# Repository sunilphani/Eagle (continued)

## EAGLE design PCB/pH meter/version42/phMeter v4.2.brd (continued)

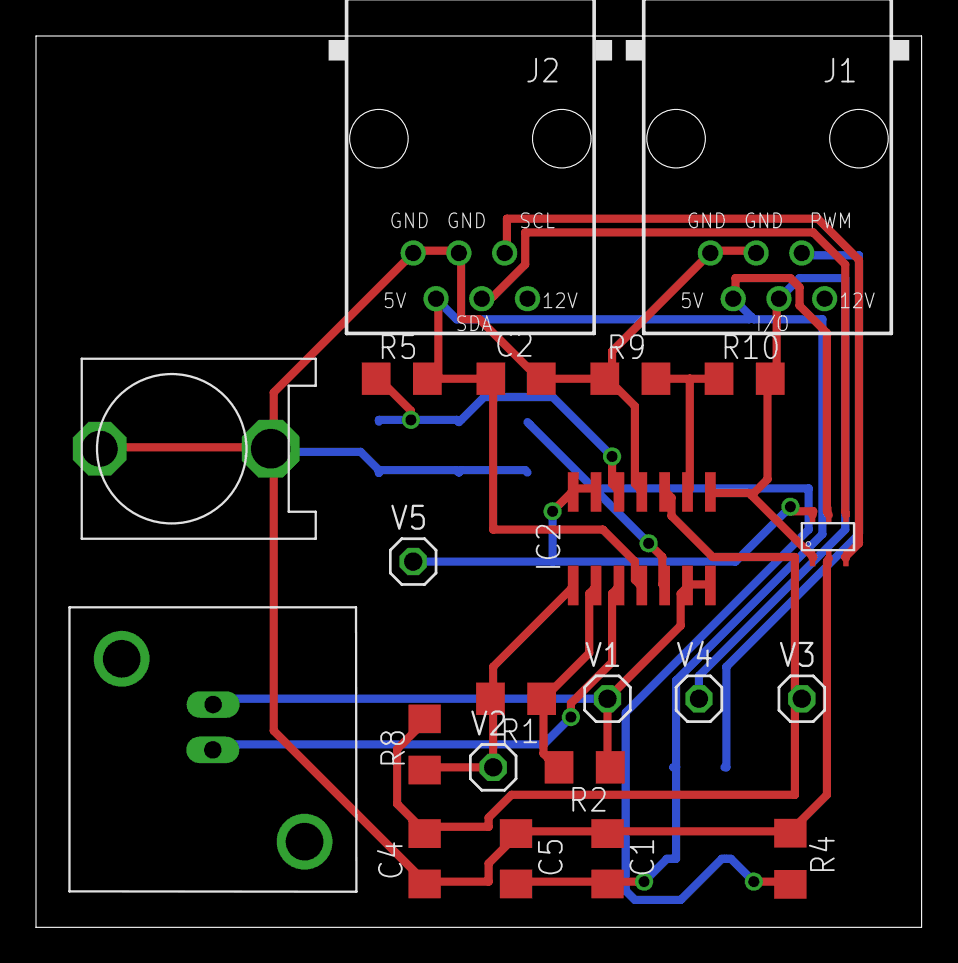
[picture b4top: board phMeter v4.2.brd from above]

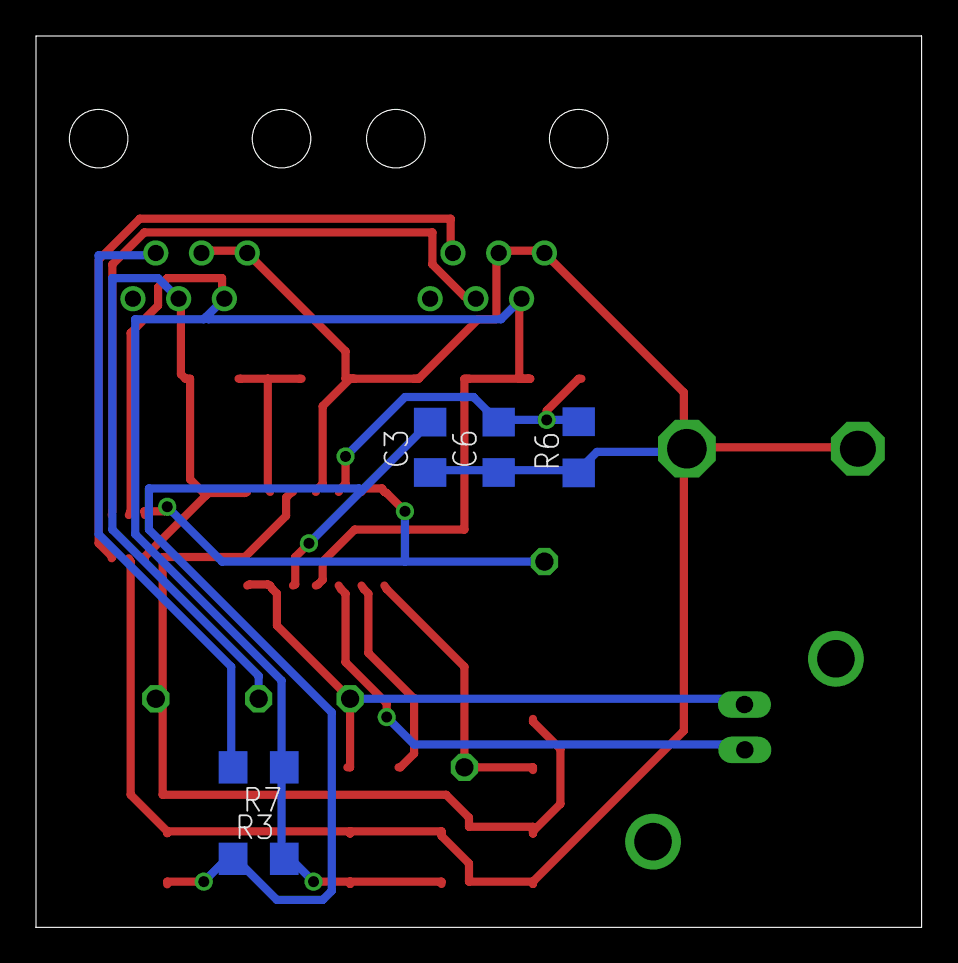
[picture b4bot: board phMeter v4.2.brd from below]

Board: 2 copper layers, 49.2 x 49.5 mm, 27 parts (5 on the bottom side), 15 nets.

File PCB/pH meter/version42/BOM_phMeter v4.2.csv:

"Qty";"Value";"Device";"Package";"Parts";"Description";"";
"5";"";"PINHD-1X1";"1X01";"V1, V2, V3, V4, V5";"PIN HEADER";"";
"1";"0.000010";"C-EUC1206";"C1206";"C5";"CAPACITOR, European symbol";"";
"4";"100k";"R-EU_R1206";"R1206";"R2, R3, R4, R6";"RESISTOR, European symbol";"";
"4";"100n";"C-EUC1206";"C1206";"C1, C2, C3, C6";"CAPACITOR, European symbol";"";
"1";"110k";"R-EU_R1206";"R1206";"R9";"RESISTOR, European symbol";"";
"1";"124k";"R-EU_R1206";"R1206";"R1";"RESISTOR, European symbol";"";
"1";"1k";"R-EU_R1206";"R1206";"R7";"RESISTOR, European symbol";"";
"1";"2.2k";"R-EU_R1206";"R1206";"R8";"RESISTOR, European symbol";"";
"1";"22000n";"C-EUC1206";"C1206";"C4";"CAPACITOR, European symbol";"";
"1";"240k";"R-EU_R1206";"R1206";"R5";"RESISTOR, European symbol";"";
"1";"750";"R-EU_R1206";"R1206";"R10";"RESISTOR, European symbol";"";
"1";"BNC-VERTICAL";"BNC-VERTICAL";"BNC-VERTICAL";"U$1";"";"";
"1";"MCP3425";"MCP3425";"SOT-23-6";"U$5";"";"";
"1";"RJ12STRAIGHT";"RJ12STRAIGHT";"RJ12-STRAIGHT";"J1";"CORCOM Modular RJ Jacks No Shield";"";
"1";"RJ12STRAIGHT-I2C";"RJ12STRAIGHT-I2C";"RJ12-STRAIGHT-I2C";"J2";"CORCOM Modular RJ Jacks No Shield";"";
"1";"TL084D";"TL084D";"SO14";"IC2";"OP AMP";"";
"1";"VERTICAL-JACK";"VERTICAL-JACK";"VERTICAL-JACK";"U$3";"";"";

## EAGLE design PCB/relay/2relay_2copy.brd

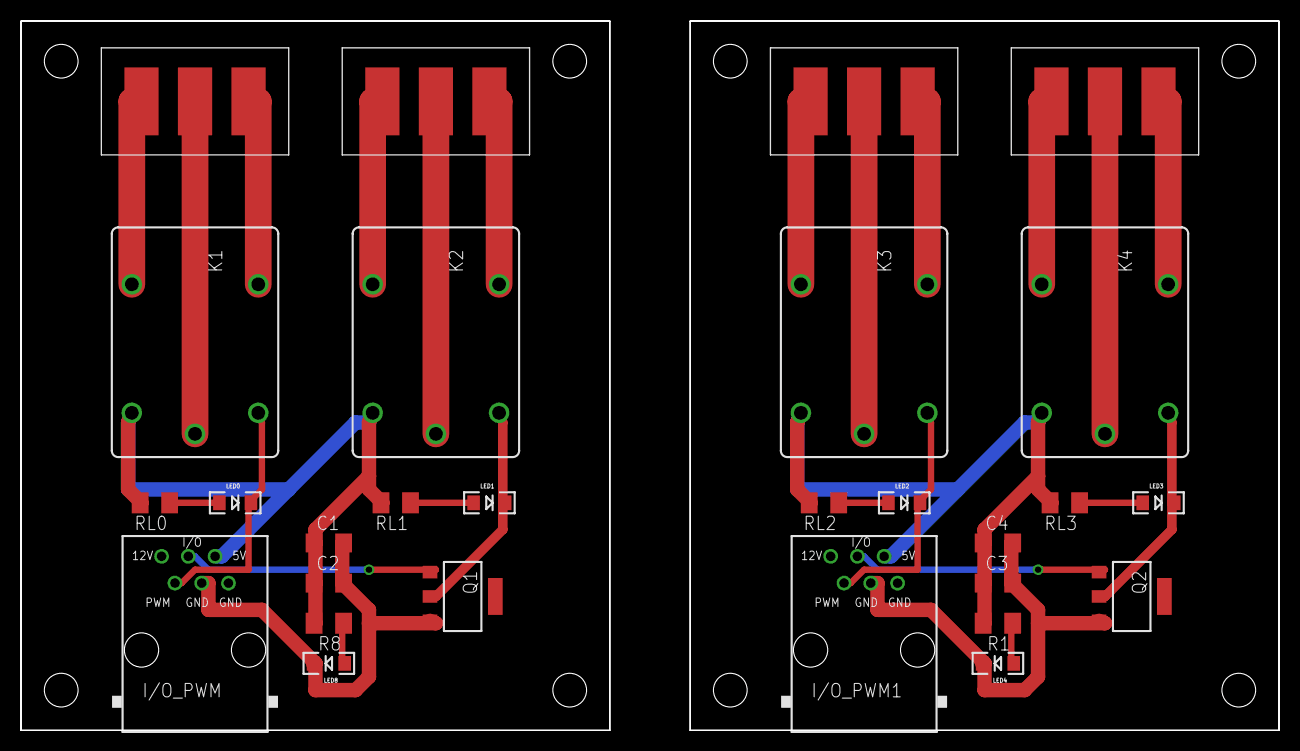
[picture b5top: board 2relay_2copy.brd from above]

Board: 2 copper layers, 119.4 x 67.3 mm, 28 parts (0 on the bottom side), 28 nets.

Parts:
C1, C4: 10uF; C1206
C2, C3: 100nF; C1206
I/O_PWM, I/O_PWM1: I2C 1; RJ12-STRAIGHT
K1, K2, K3, K4: JS-M1-9V-5; JS-M
LED0, LED1, LED2, LED3, LED4, LED8: LED-1206
Q1, Q2: BSP75; PG-SOT-223
R1, R8: 1K; M1206
RL0, RL1, RL2, RL3: 1K; M1206
X1, X2, X3, X4: 22-23-20315.08S; 3-PIN-5.08S

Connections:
+5V: C1.1, C2.1, I/O_PWM.+5V, K1.2, K2.2, R8.2, RL0.2, RL1.2
+5V1: C3.1, C4.1, I/O_PWM1.+5V, K3.2, K4.2, R1.2, RL2.2, RL3.2
GND: C1.2, C2.2, I/O_PWM.GND2, LED8.C, Q1.3
GND1: C3.2, C4.2, I/O_PWM1.GND2, LED4.C, Q2.3
I/O: I/O_PWM.I/O, Q1.1
I/O1: I/O_PWM1.I/O, Q2.1
unnamed: K2.1, LED1.C, Q1.2
unnamed: LED0.A, RL0.1
unnamed: K4.1, LED3.C, Q2.2
unnamed: LED1.A, RL1.1
unnamed: K2.C, X1.2
unnamed: K1.NC, X2.3
unnamed: K2.NC, X1.3
unnamed: LED2.A, RL2.1
unnamed: LED3.A, RL3.1
unnamed: LED4.A, R1.1
unnamed: K4.NO, X3.1
unnamed: K3.NO, X4.1
unnamed: K3.NC, X4.3
unnamed: K2.NO, X1.1
unnamed: K4.NC, X3.3
unnamed: K4.C, X3.2
unnamed: K1.NO, X2.1
unnamed: LED8.A, R8.1
POWER1: K1.C, X2.2
POWER2: K3.C, X4.2
PWM: I/O_PWM.PWM, K1.1, LED0.C
PWM1: I/O_PWM1.PWM, K3.1, LED2.C

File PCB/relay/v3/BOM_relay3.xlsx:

Qty | Value | Device | Package | Parts | Description
2 |  | JP1Q | JP1 | JP_+12V
3 |  | LED1206 | LED-1206 | LED0
1 | 100nF | C-EUC1206 | C1206 | C2 | CAPACITOR
1 | 10uF | C-EUC1206 | C1206 | C1 | CAPACITOR
3 | 1K | R-EU_M1206 | M1206 | R8
2 | 22-23-20315.08S | 22-23-20315.08S | 3-PIN-5.08S | X1
1 | BSP75 | BSP613P | PG-SOT-223 | Q1 | SIPMOS (R) Small-Signal-Transistor P-Channel (2 Drain)
1 | I2C 1 | RJ12STRAIGHT | RJ12-STRAIGHT | I/O_PWM | CORCOM Modular RJ Jacks No Shield
2 | JS-M1-9V-5 | JS-M1-9V-5 | JS-M | K1

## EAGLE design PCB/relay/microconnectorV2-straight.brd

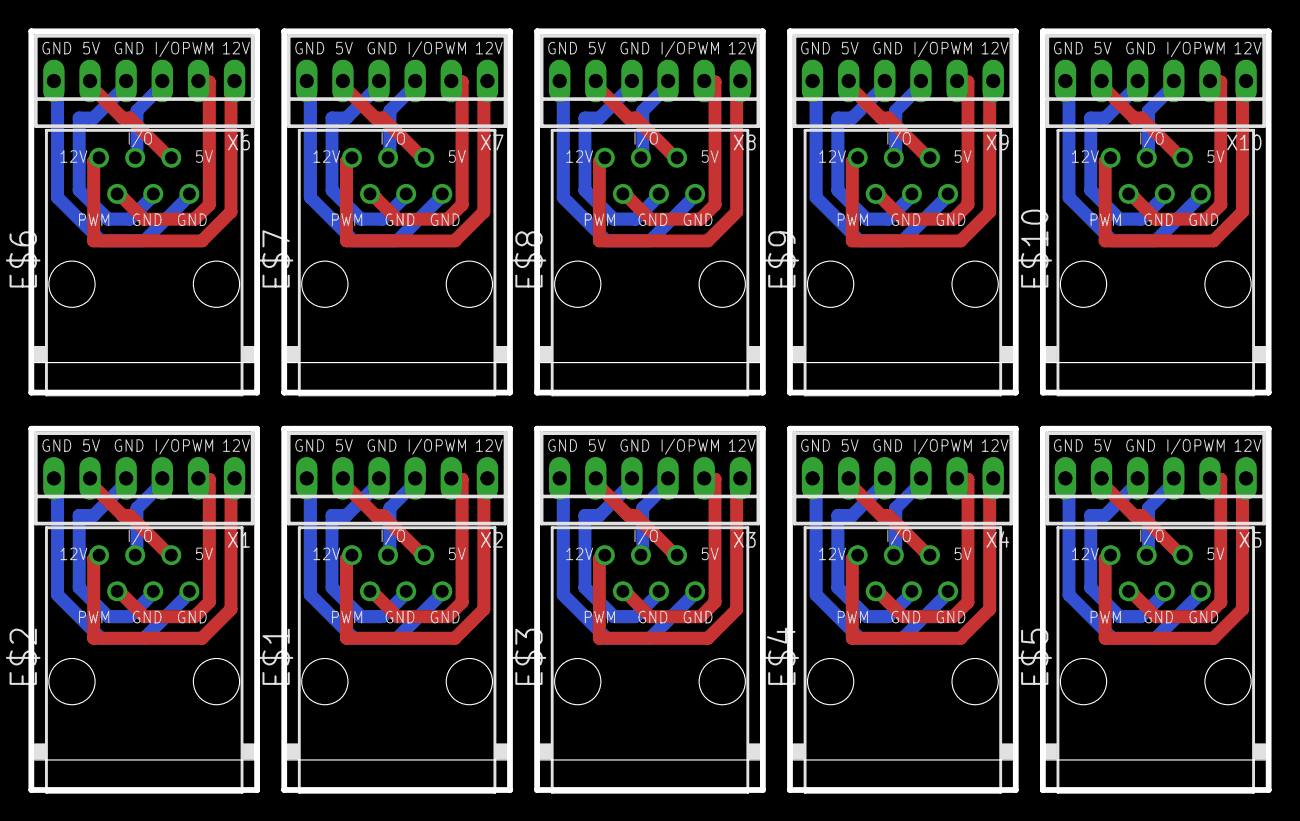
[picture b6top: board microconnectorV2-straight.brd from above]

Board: 2 copper layers, 87.0 x 53.3 mm, 20 parts (0 on the bottom side), 60 nets.

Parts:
E$1, E$2, E$3, E$4, E$5, E$6, E$7, E$8, E$9, E$10: RJ12-STRAIGHT
X1, X2, X3, X4, X5, X6, X7, X8, X9, X10: 22-23-2061

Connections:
S$1: E$2.GND1, X1.6
S$2: E$2.+5V, X1.5
S$3: E$2.GND2, X1.4
S$4: E$2.I/O, X1.3
S$5: E$2.PWM, X1.2
S$6: E$2.+12V, X1.1
S$7: E$1.GND1, X2.6
S$8: E$1.+5V, X2.5
S$9: E$1.GND2, X2.4
S$10: E$1.I/O, X2.3
S$11: E$1.PWM, X2.2
S$12: E$1.+12V, X2.1
S$13: E$3.GND1, X3.6
S$14: E$3.+5V, X3.5
S$15: E$3.GND2, X3.4
S$16: E$3.I/O, X3.3
S$17: E$3.PWM, X3.2
S$18: E$3.+12V, X3.1
S$19: E$4.GND1, X4.6
S$20: E$4.+5V, X4.5
S$21: E$4.GND2, X4.4
S$22: E$4.I/O, X4.3
S$23: E$4.PWM, X4.2
S$24: E$4.+12V, X4.1
S$25: E$5.GND1, X5.6
S$26: E$5.+5V, X5.5
S$27: E$5.GND2, X5.4
S$28: E$5.I/O, X5.3
S$29: E$5.PWM, X5.2
S$30: E$5.+12V, X5.1
S$31: E$6.GND1, X6.6
S$32: E$6.+5V, X6.5
S$33: E$6.GND2, X6.4
S$34: E$6.I/O, X6.3
S$35: E$6.PWM, X6.2
S$36: E$6.+12V, X6.1
S$37: E$7.GND1, X7.6
S$38: E$7.+5V, X7.5
S$39: E$7.GND2, X7.4
S$40: E$7.I/O, X7.3
S$41: E$7.PWM, X7.2
S$42: E$7.+12V, X7.1
S$43: E$8.GND1, X8.6
S$44: E$8.+5V, X8.5
S$45: E$8.GND2, X8.4
S$46: E$8.I/O, X8.3
S$47: E$8.PWM, X8.2
S$48: E$8.+12V, X8.1
S$49: E$9.GND1, X9.6
S$50: E$9.+5V, X9.5
S$51: E$9.GND2, X9.4
S$52: E$9.I/O, X9.3
S$53: E$9.PWM, X9.2
S$54: E$9.+12V, X9.1
S$55: E$10.GND1, X10.6
S$56: E$10.+5V, X10.5
S$57: E$10.GND2, X10.4
S$58: E$10.I/O, X10.3
S$59: E$10.PWM, X10.2
S$60: E$10.+12V, X10.1
